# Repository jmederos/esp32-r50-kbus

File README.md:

# ESP32 K-bus Interface

[![MPL 2.0 License][license-shield]][license-url]
[![LinkedIn][linkedin-shield]][linkedin-url]

## Table of Contents

* [About the Project](#about)
  * [Hardware](#hardware)
  * [Software](#software)
* [Getting Started](#getting-started)
  * [Prerequisites](#prerequisites)
  * [Building](#building)
  * [Installing](#installing)
* [Roadmap](#roadmap)
* [License](#license)

## About

K-bus/I-bus to Bluetooth bridge for Mini/BMWs. Developed on esp-idf 4.0.2 and a 2006 Mini Cooper. Main goal was to get AVRCP control from steering wheel to iPhone; going forward looking to make it a platform for emulating K-bus devices.

### Hardware

See [hardware](hardware) folder

### Software

* [esp-idf](https://github.com/espressif/esp-idf)
* [btstack](https://github.com/bluekitchen/btstack)

<!-- GETTING STARTED -->
## Getting Started

Clone, build, and flash.

### Prerequisites

Install `esp-idf` and the ESP32 `btstack` port by following the respective instructions.

### Building

#### Hardware

**TBD**

#### Software

* Clone this repo and its submodules `git clone --recursive https://github.com/jmederos/esp32-r50-kbus.git`
* After installing prequisites, run the helper script `./tools/build.sh` to compile
* `./tools/flash_monitor.sh` to load onto ESP32 and run `idf.py monitor`
_Note: Helper scripts in tools folder assume a WSL Ubuntu install w/ESP32 on Windows COM4_

### Installing

* Use OEM CD changer pre-wiring in R50 behind right side panel in trunk.

#### R50 Support Docs
* [How to find pre-wiring](https://www.northamericanmotoring.com/forums/navigation-and-audio/224408-can-t-find-cd-changer-pre-wiring.html)
* [CD changer installation instructions](https://new.minimania.com/images/instructions/OEM%20CD%20Changer.pdf)

## Roadmap
| Feature | Status | Notes |
| --- | --- | --- |
| Software POC: control phone via AVRCP w/o A2DP advertised. | 👌🏽 | _Although part of the BT spec, example implementations on AVRCP-only are hard to come by._ |
| Hardware POC: acquire + test k-line transceivers. | 🙌🏽 |   |
| K-bus proof concept, pickup MFL messages. | 👍🏽 | _Works in vehicle, works in mockup w/Navcoder + iPhone streaming to a BT headphone amp._ |
| Write to radio head unit display | 🥳 | _Seems to work, now let's do scrolling display_ |
| SDRS Emulation | 👍🏽 | _Functional, didn't really like the fact that FiiO BT amp didn't shutdown with car; will stick to aux input + `TEL` display updates for now._ |
| Write to radio head unit display | 🥳 | _Seems to work, now let's do scrolling display_ |
| [AMS](https://developer.apple.com/library/archive/documentation/CoreBluetooth/Reference/AppleMediaService_Reference/Specification/Specification.html) instead of AVRCP |   | _Didn't know this was a thing, seems like a better bet; btstack + esp-idf is a little clunky._ |
| [ANCS](https://developer.apple.com/library/archive/documentation/CoreBluetooth/Reference/AppleNotificationCenterServiceSpecification/Introduction/Introduction.html) Support & update radio display w/push notification | 🤞 |   |

_See the [open issues](https://github.com/jmederos/esp32-r50-kbus/issues) for a list of proposed features (and known issues)._

## References
* [iPod ↔ Sirius IBus adapter](https://github.com/blalor/iPod_IBus_adapter) - _Referenced for SDRS packet logs (my car isn't equiped with one.)_
* [Hack The IBus](http://web.archive.org/web/20110320205413/http://ibus.stuge.se/Main_Page)

## License

Distributed under the MPL 2.0 License. See `LICENSE` for more information.

<!-- MARKDOWN LINKS & IMAGES -->
<!-- https://www.markdownguide.org/basic-syntax/#reference-style-links -->
[license-shield]: https://img.shields.io/badge/license-MPL%202.0-blue
[license-url]: https://github.com/jmederos/esp32-r50-kbus/blob/master/LICENSE
[linkedin-shield]: https://img.shields.io/badge/-LinkedIn-black.svg?style=flat-square&logo=linkedin&colorB=555
[linkedin-url]: https://linkedin.com/in/jacobmederos

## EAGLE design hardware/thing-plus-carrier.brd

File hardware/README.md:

# Hardware

## Microcontroller
* [Sparkfun MicroMod ESP32](https://www.sparkfun.com/products/16781)
* [Sparkfun MicroMod ATP Board](https://www.sparkfun.com/products/16885)

## Power Regulation
| Part | Notes |
| --- | --- |
| ~~[On Semi NCV7805BTG 5V Regulator](https://www.digikey.com/en/products/detail/on-semiconductor/921437)~~ | Too inefficient
| [USB Power Supply](https://www.amazon.com/gp/product/B07KWRH61D) | Worked well for prototyping w/MicroMod ESP32
| [OKI-78SR-5](https://www.digikey.com/en/products/detail/OKI-78SR-5-1-5-W36H-C/3438675) | For v1 of feather board

## Transciever ICs
| Part | Status | Notes |
| --- | --- | --- |
| [ON Semi NCV7428D13R2G](https://www.digikey.com/en/products/detail/on-semiconductor/5022588) | 🤷🏽‍♂️ | Have it; still untested. |
| [NXP TJA1021T](https://www.nxp.com/docs/en/data-sheet/TJA1021.pdf) | 👍🏽 | Using with a `CP2102` USB ⇄ Serial to interface with NavCoder and simulate bus on desktop. |
| [TI SN65HVDA195QDRQ1](https://www.digikey.com/en/products/detail/texas-instruments/2094636) | 👎🏽 | Used on initial in-car perfboard prototypes. Works ok, but susceptible to glitching the bus (doors randomly unlocked); doesn't have tx timeout or contention detection. Best used to create a simulated bus as the controlling node like the `NXP` part above. |
| [Microchip MCP2025](https://www.digikey.com/en/products/detail/microchip-technology/3543134) | 🤷🏽‍♂️ | Have it; unlikely to test/use it. Doesn't have failsafe features and isn't pin-compatible w/`TI` |
| [Microchip MCP2004(A)](https://www.digikey.com/en/products/detail/MCP2004AT-E-SN/2803651) | 👍🏽 | Selected for tx timeout and bus contention detection + added bonus of `FAULT` pin. Also pin compatible with `TI` and `NXP` parts used for prototyping. So far, only tested `MCP2004A`; works in simulated bus setup. |
| [Microchip MCP2003B](https://www.digikey.com/en/products/detail/this-gets-ignored-🤷🏽‍♂️/5810590) | 🤷🏽‍♂️ | Selected for tx timeout and bus contention detection. Also pin compatible with `TI` and `NXP` parts used for prototyping. Have it; still untested. |

## Connector
The CD Changer connectors are a 3-pin power/data (all populated) and 6-pin audio (3 or 4 populated)
| Part | Notes |
| --- | --- |
| [TE AMP 1-1718346-1](https://www.newark.com/these/doNot/matter/dp/86Y2196) | Existing pre-wiring connector supplying `gnd`, `12v`, `kbus` |
| [TE AMP 1-968700-1](https://www.newark.com/these/doNot/matter/dp/86Y4923) | Matching socket for above; a row of 3 pin headers can also be used if this can't be sourced. OEM part [BMW 61 13 6 931 929](https://www.ecstuning.com/b-genuine-bmw-parts/pin-terminal/61136931929/) is order of magnitude more expensive. |
| [TE AMP 1379118-1](https://www.newark.com/these/doNot/matter/dp/69AH9772) | Matching socket for 6-pin audio connector. Depending on vehicle either 3 pin unbalanced audio or 4 pin balanced audio. |

## Board
Created a simple board for a more permanent installation

### BOM
_TODO_

### Pictures

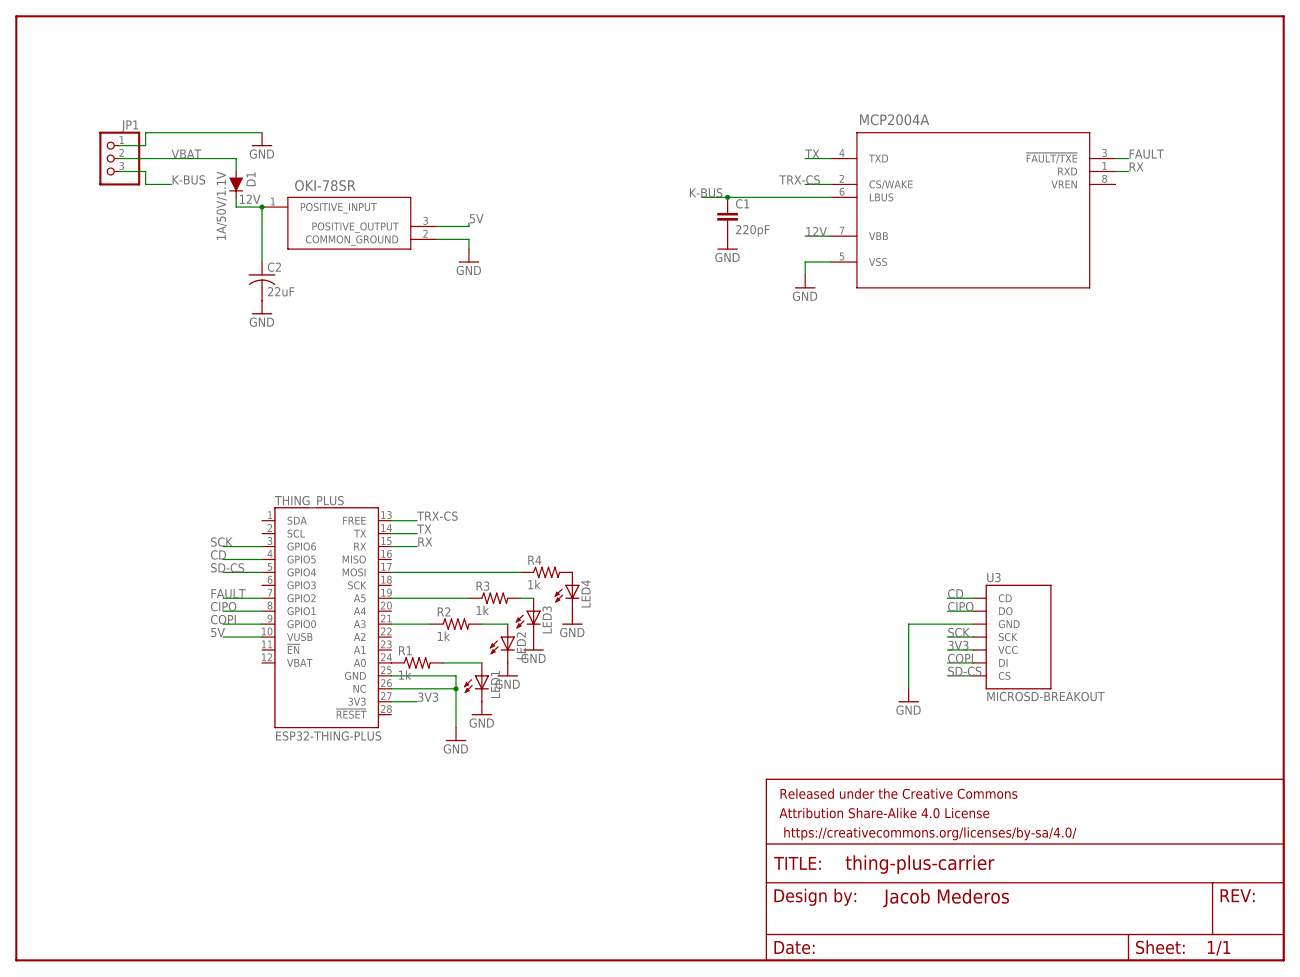
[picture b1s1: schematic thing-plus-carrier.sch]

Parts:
C1: 220pF; CAP-PTH-SMALL-KIT
C2: 22uF; C1206K
D1: 1A/50V/1.1V; DIODE-1N4001
ESP32-THING-PLUS: THING_PLUS
FRAME1: FRAME-LETTERNO_PACKAGE; DUMMY
JP1: PINHD-1X3; 1X03
LED1, LED2, LED3, LED4: LEDCHIPLED_0805; CHIPLED_0805
MCP2004A: MCP2004A-E/SNSOIC8_4P9X3P9MC_MCH-M; SOIC8_4P9X3P9MC_MCH-M
OKI-78SR: OKI-78SR-5/1.5-W36H-C; OKI-78SR-5/1.5-W36H-C_MUR
R1, R2, R3, R4: 1k; R0805
U3: MICROSD-BREAKOUT

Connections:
3V3: ESP32-THING-PLUS.27 (3V3), U3.VCC
5V: ESP32-THING-PLUS.10 (VUSB), OKI-78SR.3 (POSITIVE_OUTPUT)
12V: C2.1, D1.C, MCP2004A.7 (VBB), OKI-78SR.1 (POSITIVE_INPUT)
CD: ESP32-THING-PLUS.4 (GPIO5), U3.CD
CIPO: ESP32-THING-PLUS.8 (GPIO1), U3.DO
COPI: ESP32-THING-PLUS.9 (GPIO0), U3.DI
FAULT: ESP32-THING-PLUS.7 (GPIO2), MCP2004A.3 (!FAULT/TXE)
GND: C1.2, C2.2, ESP32-THING-PLUS.25 (GND), ESP32-THING-PLUS.26 (NC), JP1.1, LED1.C, LED2.C, LED3.C, LED4.C, MCP2004A.5 (VSS), OKI-78SR.2 (COMMON_GROUND), U3.GND
K-BUS: C1.1, JP1.3, MCP2004A.6 (LBUS)
unnamed: ESP32-THING-PLUS.19 (A5), R3.1
unnamed: ESP32-THING-PLUS.24 (A0), R1.1
unnamed: ESP32-THING-PLUS.21 (A3), R2.1
unnamed: ESP32-THING-PLUS.17 (MOSI), R4.1
unnamed: LED4.A, R4.2
unnamed: LED3.A, R3.2
unnamed: LED2.A, R2.2
unnamed: LED1.A, R1.2
RX: ESP32-THING-PLUS.15 (RX), MCP2004A.1 (RXD)
SCK: ESP32-THING-PLUS.3 (GPIO6), U3.SCK
SD-CS: ESP32-THING-PLUS.5 (GPIO4), U3.CS
TRX-CS: ESP32-THING-PLUS.13 (FREE), MCP2004A.2 (CS/WAKE)
TX: ESP32-THING-PLUS.14 (TX), MCP2004A.4 (TXD)
VBAT: D1.A, JP1.2

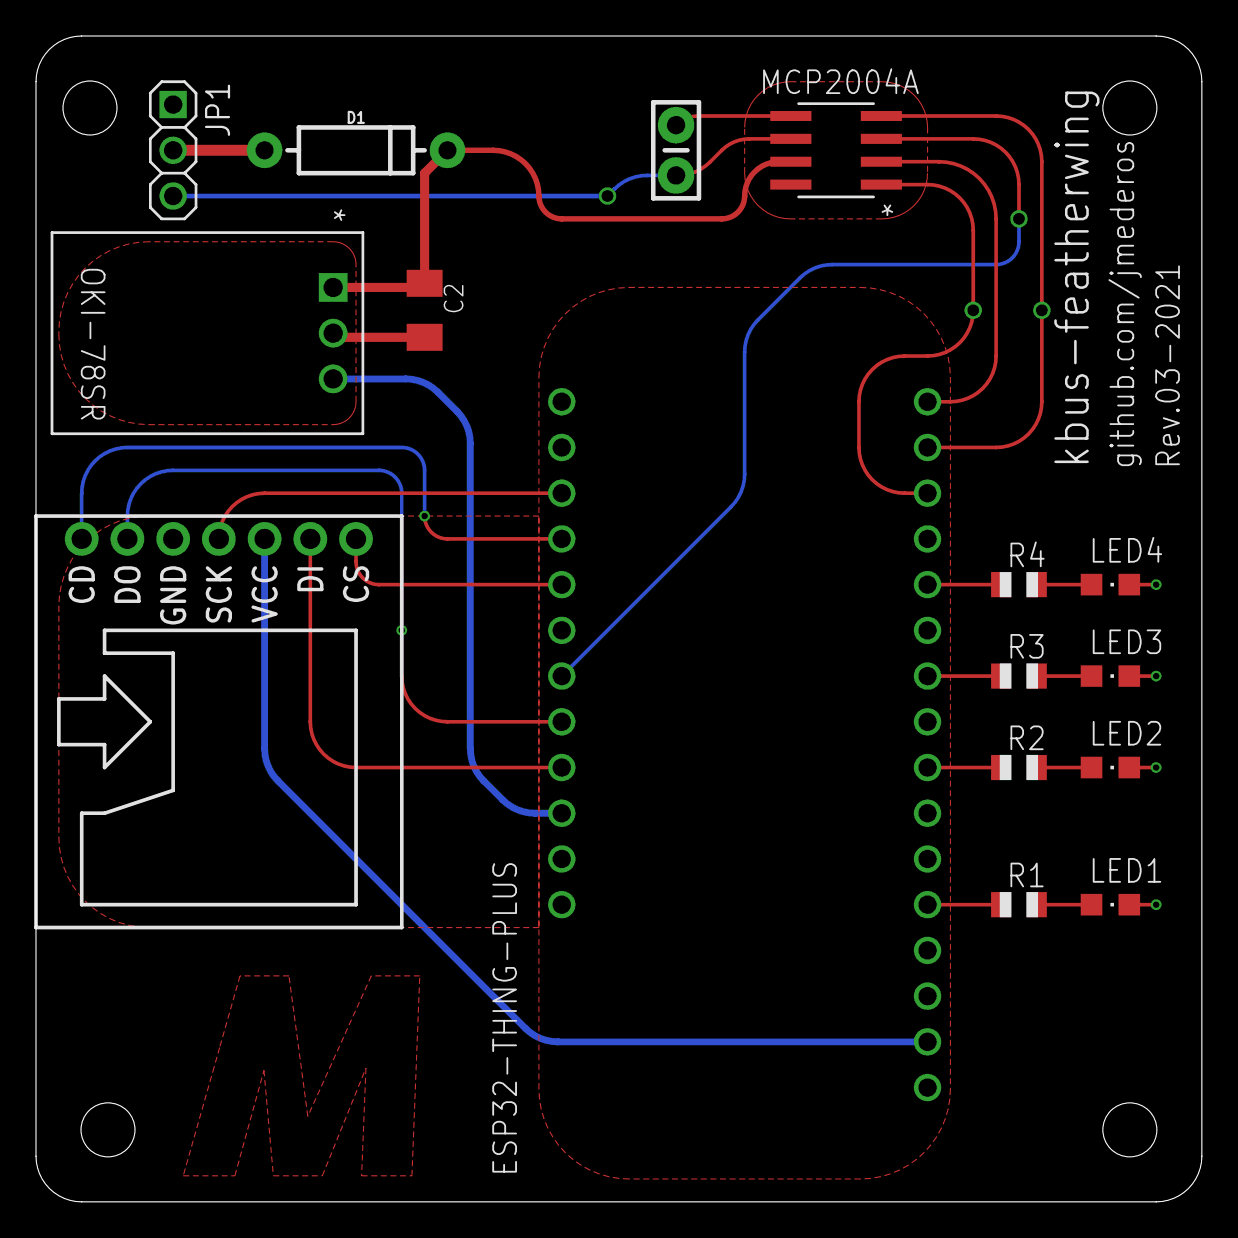
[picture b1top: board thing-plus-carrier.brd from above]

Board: 2 copper layers, 64.8 x 64.8 mm, 17 parts (0 on the bottom side), 23 nets.

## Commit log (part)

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2020-11-07 Initial commit 🎉🥳
2020-11-21 WIP CMake + Components
2020-12-07 Added esphttpd + espfs as git submodules. Sorted out compilation errors.
2020-12-08 WIP—Refactored bt component; added server task stub; added simple build scripts
2020-12-09 WIP—Added wifi AP component. btstack + wifi not coexisting properly
2020-12-10 WIP—UART Driver component, configured ESP32 for multicore FreeRTOS
2020-12-11 Readme updates, UART tested working with USB adapter and terminal
2020-12-14 Added kbus service component. 'Device Status Ready' message shows up on NavCoder🎉
2020-12-14 Added kbus message encoder, removed KBUS_TX_TEST_IS_ENABLED code, added #defines for kbus addresses
2020-12-16 Added kbus command list, updated CDC emulation
2020-12-16 Refactor kbus driver & service to use queues
2020-12-16 Higher level kbus message parsing. Started to add BT queue for requesting AVRCP commands from bt component
2020-12-16 Added MFL message handling code, tested working w/NavCoder
2020-12-16 Basic AVRCP working w/NavCoder and iPhone 🥳
2020-12-17 readme update
2020-12-19 Added menuconfig support for BT Service. Cleanup AVRCP logging & remove AVRCP Target code
2020-12-21 README update + BT/AVRCP updates
2020-12-21 Refactored uart tx from function call to queue
2020-12-21 CDC emu now responds to status requests; refactored kbus_message_t, elminated 2 bytes per message by not storing chksum & msg_len
2020-12-29 Added ENABLE Pin to uart driver, updated CDC emulation, changed logging verbosity, removed broadcast message handling
2020-12-29 General implementation for sending Device Status Ready packets
2020-12-31 Debugging stuck messages... Seems ESP-IDF rx fifo doesn't flush into queue
2020-12-31 Refactored UART RX code, solved panic & timing issue
2021-01-02 Added bt auto-reconnect task
2021-01-03 UART driver documentation
2021-01-04 SDRS Emulation
2021-01-04 UART driver improvements: drop large messages, filter by command bitmask
2021-01-04 sdrs emulator as standalone component running on seperate task (works! 🥳). Fixed UART driver accidentally masking MFL commands
2021-01-07 WIP avrcp text info
2021-01-11 AVRCP Track info pretty much working; need to implement long text scrolling
2021-01-11 Documentation update
2021-01-11 Accidentally removed bt_info_task()
2021-01-12 Scrolling now playing info
2021-01-13 removing kbus_uart_driver files
2021-01-13 adding kbus_uart_driver submodule
2021-02-11 Scrolling update + comment clarifcation
2021-02-11 starting on featherwing board
2021-02-28 laying out featherwing schematic
2021-03-02 README.md updated from https://stackedit.io/
2021-03-02 hardware/README.md created from https://stackedit.io/
2021-03-02 hardware/README.md updated from https://stackedit.io/
2021-03-02 Finished rev.1 board []~(￣▽￣)~* ; Updated docs
2021-03-13 Fixed documentation, added pics, fixed `AUTOCONNECT` compilation error when undefined in `sdkconfig`
2021-03-13 Delete hardware/images directory
    oops
2021-03-14 Delete hardware/images directory
    oops (+1 squashed commits)
    Squashed commits:
    [556f3a2] Fixed documentation, added pics, fixed `AUTOCONNECT` compilation error when undefined in `sdkconfig`
2021-03-14 Added images
2021-03-14 update pics
2021-03-14 board images
2021-03-14 More hardware documentation
2021-03-19 Displays special character, prints play/connection state to MID, some refactoring
2025-10-06 Updated for ESP-IDF v5.5 + ANCS && AMS work-in-progress

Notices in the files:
parts and their libraries:
SparkFun-Capacitors: Licensing: Creative Commons ShareAlike 4.0 International - https://creativecommons.org/licenses/by-sa/4.0
COPYRIGHT: Copyright (C) 2018 Accelerated Designs. All rights reserved
SparkFun-Aesthetics: Released under the Creative Commons Attribution Share-Alike 4.0 License
